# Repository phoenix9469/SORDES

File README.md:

## Sordes Motherboard SMT Version
### Schematic

### PCB

### 3D Top

### 3D Bottom

### Main MCU
ESP32_WROOM_32D
Internal Antenna
### Battery Charging
TP4056 Li-Ion Battery Charging Circuit(1A)
### DC-DC
SX1308 DC-DC Step Up Convertor(1.2MHz,2A)
3.7v~4.2v(Battery) to 5v(Logic)
### Weight measurement
HX711 24-Bit ADC for Weigh Scales
## Sordes LCD Board SMT Version
### Schematic

### PCB

### 3D Top

### 3D Bottom

### Main MCU
ESP32_WROOM_32D
Internal Antenna
### Pinmap
3.3V -> VCC  
GND -> GND  
GPIO15 -> CS  
GPIO4 -> RESET  
GPIO2 - > DC/RS  
GPIO23 -> SDI(MOSI),T_DIN  
GPIO18 -> SCK,T_CLK  
GPIO32 -> LED  
GPIO21 -> T_CS  
GPIO19 -> T_DO  
GPIO27 -> T_IRQ

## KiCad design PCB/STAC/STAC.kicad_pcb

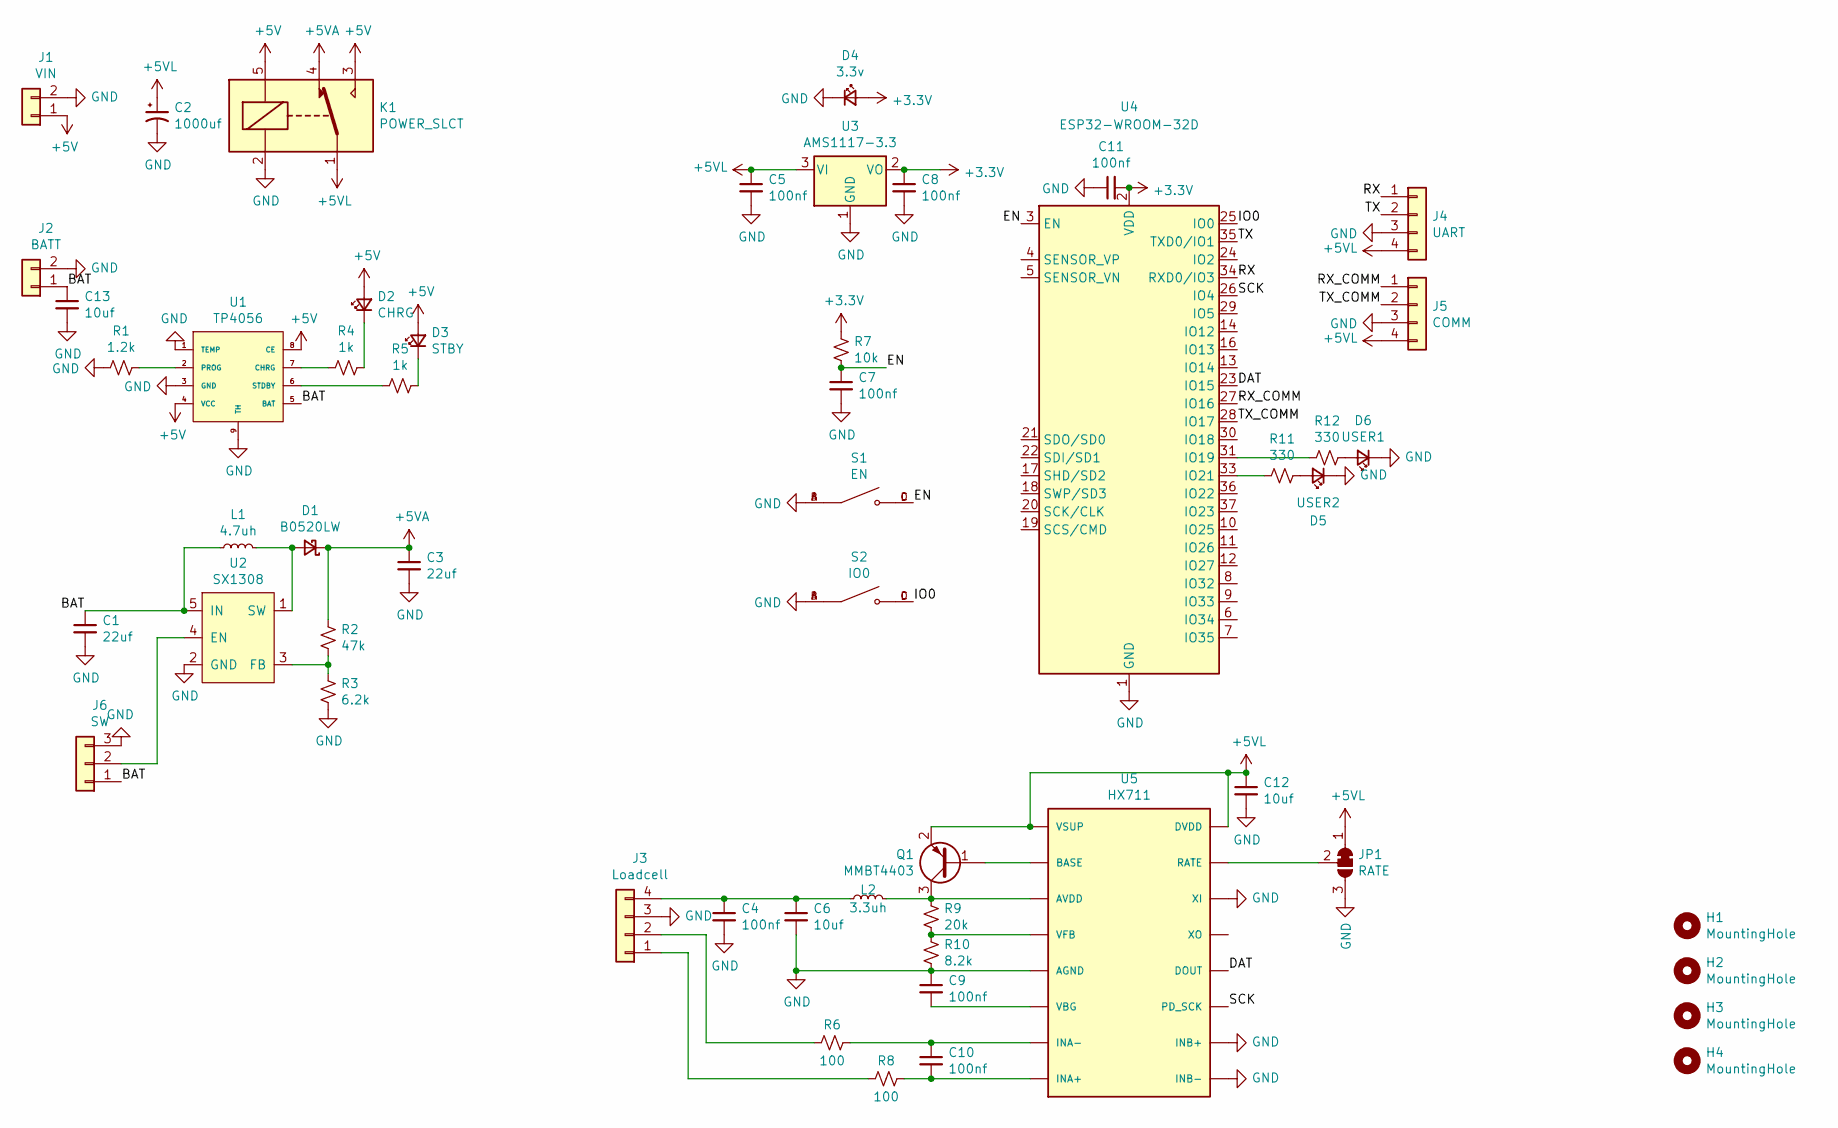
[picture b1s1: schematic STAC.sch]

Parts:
C1, C3: 22uf; C_0805_2012Metric
C2: 1000uf; CP_Elec_8x10
C4, C5, C7, C8, C9, C10, C11: 100nf; C_0603_1608Metric
C6, C12, C13: 10uf; C_0805_2012Metric
D1: B0520LW; D_SOD-123
D2: CHRG; LED_0603_1608Metric
D3: STBY; LED_0603_1608Metric
D4: 3.3v; LED_0603_1608Metric
D5: USER2; LED_0603_1608Metric
D6: USER1; LED_0603_1608Metric
H1, H2, H3, H4: MountingHole; MountingHole_3.2mm_M3
J1: VIN; Molex_PicoBlade_53261-0271_1x02-1MP_P1.25mm_Horizontal
J2: BATT; Molex_PicoBlade_53261-0271_1x02-1MP_P1.25mm_Horizontal
J3: Loadcell; Molex_PicoBlade_53261-0471_1x04-1MP_P1.25mm_Horizontal
J4: UART; Molex_PicoBlade_53261-0471_1x04-1MP_P1.25mm_Horizontal
J5: COMM; Molex_PicoBlade_53261-0471_1x04-1MP_P1.25mm_Horizontal
J6: SW; Molex_PicoBlade_53261-0371_1x03-1MP_P1.25mm_Horizontal
JP1: RATE; SolderJumper-3_P1.3mm_Bridged12_RoundedPad1.0x1.5mm_NumberL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
K1: POWER_SLCT; Relay_SPDT_SANYOU_SRD_Series_Form_C
L1: 4.7uh; L_6.3x6.3_H3
L2: 3.3uh; L_0603_1608Metric
Q1: MMBT4403; SOT-23
R1: 1.2k; R_0603_1608Metric
R2: 47k; R_0603_1608Metric
R3: 6.2k; R_0603_1608Metric
R4, R5: 1k; R_0603_1608Metric
R6, R8: 100; R_0603_1608Metric
R7: 10k; R_0603_1608Metric
R9: 20k; R_0603_1608Metric
R10: 8.2k; R_0603_1608Metric
R11, R12: 330; R_0603_1608Metric
S1: EN; SW_TS-1187A-B-A-B; PARTREV A0
S2: IO0; SW_TS-1187A-B-A-B; PARTREV A0
U1: TP4056; SOIC-8-1EP_3.9x4.9mm_P1.27mm_EP2.29x3mm_ThermalVias
U2: SX1308; SOT-23-6
U3: AMS1117-3.3; SOT-223-3_TabPin2
U4: ESP32-WROOM-32D; ESP32-WROOM-32
U5: HX711; SO-16_3.9x9.9mm_P1.27mm

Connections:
+3V3: C8.1, C11.2, D4.2 (A), R7.1, U3.2 (VO), U4.2 (VDD)
+5V: D2.2 (A), D3.2 (A), J1.1, K1.3, K1.5, U1.4 (VCC), U1.8 (CE)
+5VA: C3.1, D1.1 (K), K1.4, R2.1
+5VL: C2.1, C5.1, C12.1, J4.4, J5.4, JP1.1 (A), K1.1, Q1.2 (E), U3.3 (VI), U5.1 (VSUP), U5.16 (DVDD)
/BAT: C1.1, C13.1, J2.1, J6.1, L1.1, U1.5 (BAT), U2.5 (IN)
/DAT: U4.23 (IO15), U5.12 (DOUT)
/EN: C7.1, R7.2, S1.C, S1.D, U4.3 (EN)
/IO0: S2.C, S2.D, U4.25 (IO0)
/RX: J4.1, U4.34 (RXD0/IO3)
/RX_COMM: J5.1, U4.27 (IO16)
/SCK: U4.26 (IO4), U5.11 (PD_SCK)
/TX: J4.2, U4.35 (TXD0/IO1)
/TX_COMM: J5.2, U4.28 (IO17)
GND: C1.2, C2.2, C3.2, C4.2, C5.2, C6.2, C7.2, C8.2, C9.1, C11.1, C12.2, C13.2, D4.1 (K), D5.1 (K), D6.1 (K), J1.2, J2.2, J3.3, J4.3, J5.3, J6.3, JP1.3 (B), K1.2, R1.2, R3.2, R10.2, S1.A, S1.B, S2.A, S2.B, U1.1 (TEMP), U1.3 (GND), U1.9 (TH), U2.2 (GND), U3.1 (GND), U4.1 (GND), U4.15 (GND), U4.38 (GND), U4.39 (GND), U5.5 (AGND), U5.9 (INB-), U5.10 (INB+), U5.14 (XI)
unnamed: C4.1, C6.1, J3.4, L2.1
unnamed: C9.2, U5.6 (VBG)
unnamed: C10.1, R6.1, U5.7 (INA-)
unnamed: C10.2, R8.1, U5.8 (INA+)
unnamed: D1.2 (A), L1.2, U2.1 (SW)
unnamed: D2.1 (K), R4.1
unnamed: D3.1 (K), R5.1
unnamed: D5.2 (A), R11.1
unnamed: D6.2 (A), R12.1
unnamed: J3.1, R8.2
unnamed: J3.2, R6.2
unnamed: J6.2, U2.4 (EN)
unnamed: JP1.2 (C), U5.15 (RATE)
unnamed: L2.2, Q1.3 (C), R9.1, U5.3 (AVDD)
unnamed: Q1.1 (B), U5.2 (BASE)
unnamed: R1.1, U1.2 (PROG)
unnamed: R2.2, R3.1, U2.3 (FB)
unnamed: R4.2, U1.7 (CHRG)
unnamed: R5.2, U1.6 (STDBY)
unnamed: R9.2, R10.1, U5.4 (VFB)
unnamed: R11.2, U4.33 (IO21)
unnamed: R12.2, U4.31 (IO19)

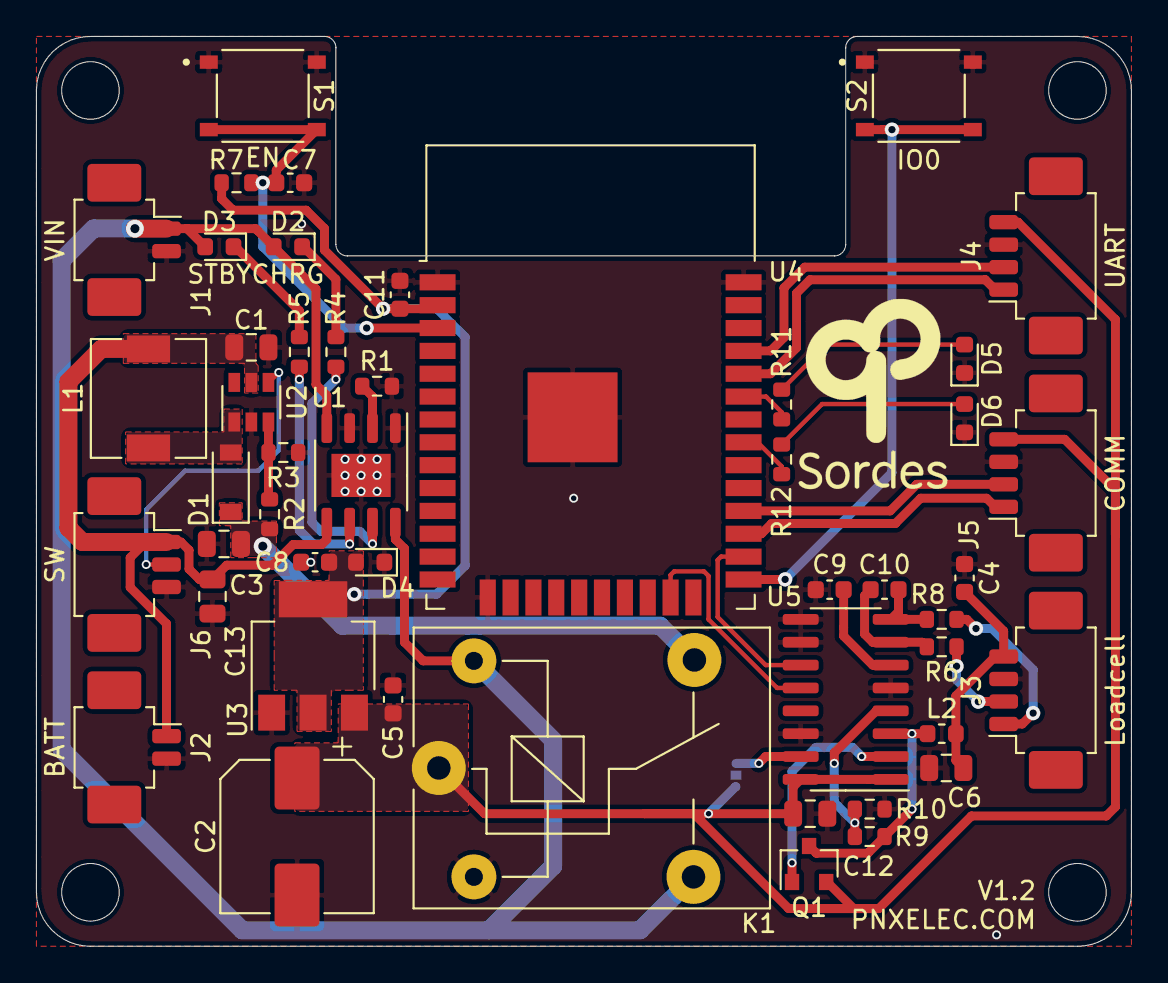
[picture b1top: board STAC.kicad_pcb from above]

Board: 2 copper layers, 60.8 x 50.5 mm, 53 parts (1 on the bottom side), 36 nets.

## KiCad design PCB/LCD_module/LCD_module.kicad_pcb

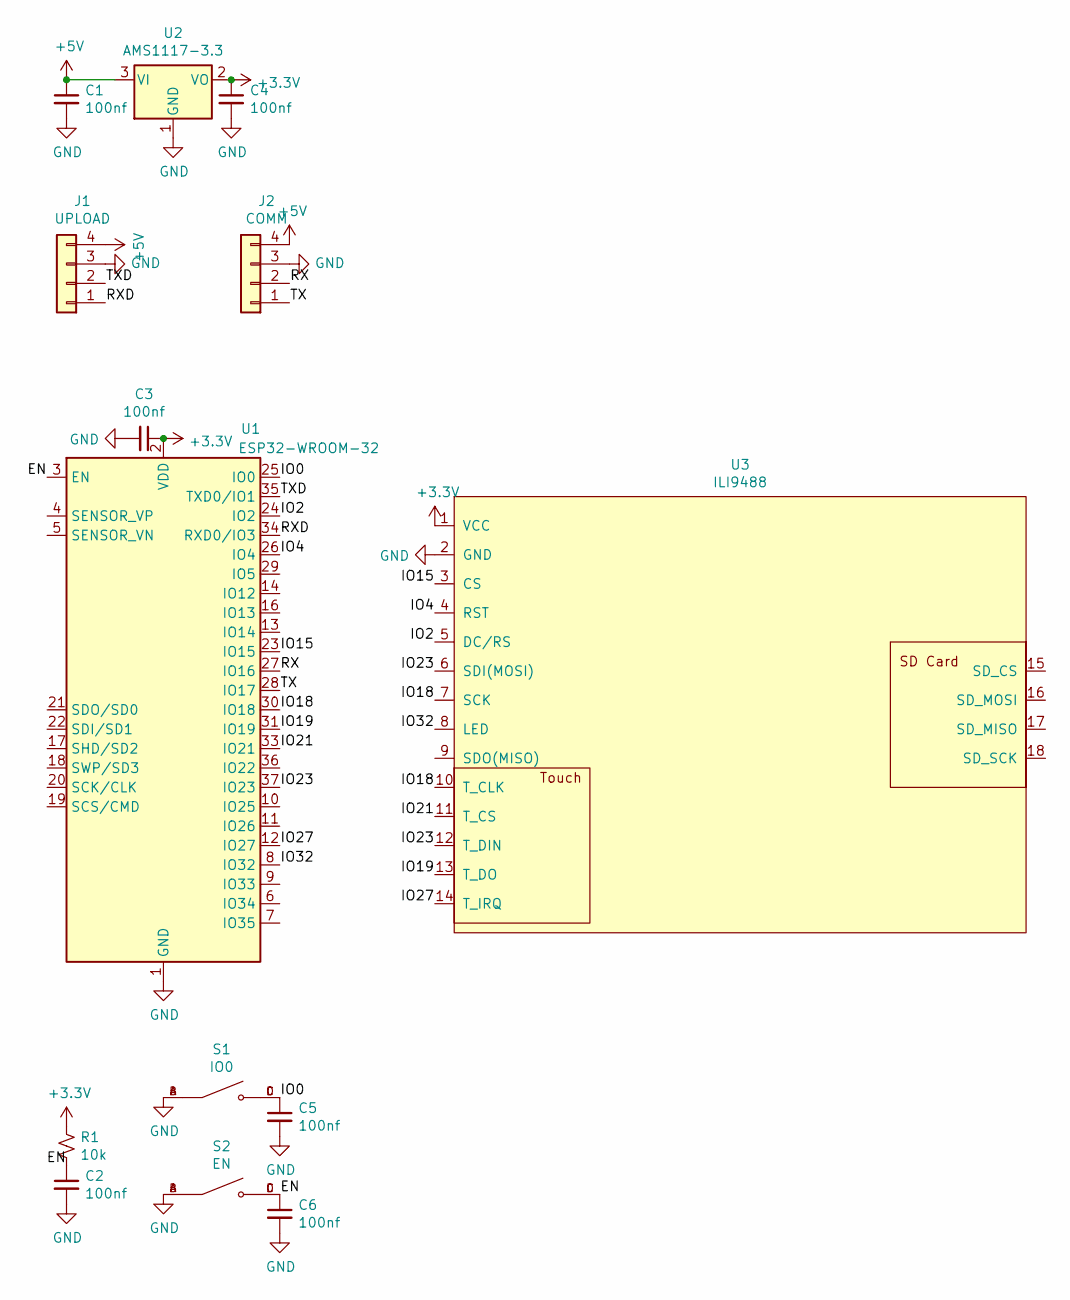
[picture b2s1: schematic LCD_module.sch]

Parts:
C1, C2, C3, C4, C5, C6: 100nf; C_0603_1608Metric
J1: UPLOAD; Molex_PicoBlade_53261-0471_1x04-1MP_P1.25mm_Horizontal
J2: COMM; Molex_PicoBlade_53261-0471_1x04-1MP_P1.25mm_Horizontal
R1: 10k; R_0603_1608Metric
S1: IO0; SW_TS-1187A-B-A-B; PARTREV A0
S2: EN; SW_TS-1187A-B-A-B; PARTREV A0
U1: ESP32-WROOM-32
U2: AMS1117-3.3; SOT-223-3_TabPin2
U3: ILI9488

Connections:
+3V3: C3.1, C4.1, R1.1, U1.2 (VDD), U2.2 (VO), U3.1 (VCC)
+5V: C1.1, J1.4, J2.4, U2.3 (VI)
/EN: C2.1, C6.1, R1.2, S2.C, S2.D, U1.3 (EN)
/IO0: C5.1, S1.C, S1.D, U1.25 (IO0)
/IO2: U1.24 (IO2), U3.5 (DC/RS)
/IO4: U1.26 (IO4), U3.4 (RST)
/IO15: U1.23 (IO15), U3.3 (CS)
/IO18: U1.30 (IO18), U3.7 (SCK), U3.10 (T_CLK)
/IO19: U1.31 (IO19), U3.13 (T_DO)
/IO21: U1.33 (IO21), U3.11 (T_CS)
/IO23: U1.37 (IO23), U3.6 (SDI(MOSI)), U3.12 (T_DIN)
/IO27: U1.12 (IO27), U3.14 (T_IRQ)
/IO32: U1.8 (IO32), U3.8 (LED)
/RX: J2.2, U1.27 (IO16)
/RXD: J1.1, U1.34 (RXD0/IO3)
/TX: J2.1, U1.28 (IO17)
/TXD: J1.2, U1.35 (TXD0/IO1)
GND: C1.2, C2.2, C3.2, C4.2, C5.2, C6.2, J1.3, J2.3, S1.A, S1.B, S2.A, S2.B, U1.1 (GND), U1.15 (GND), U1.38 (GND), U1.39 (GND), U2.1 (GND), U3.2 (GND)

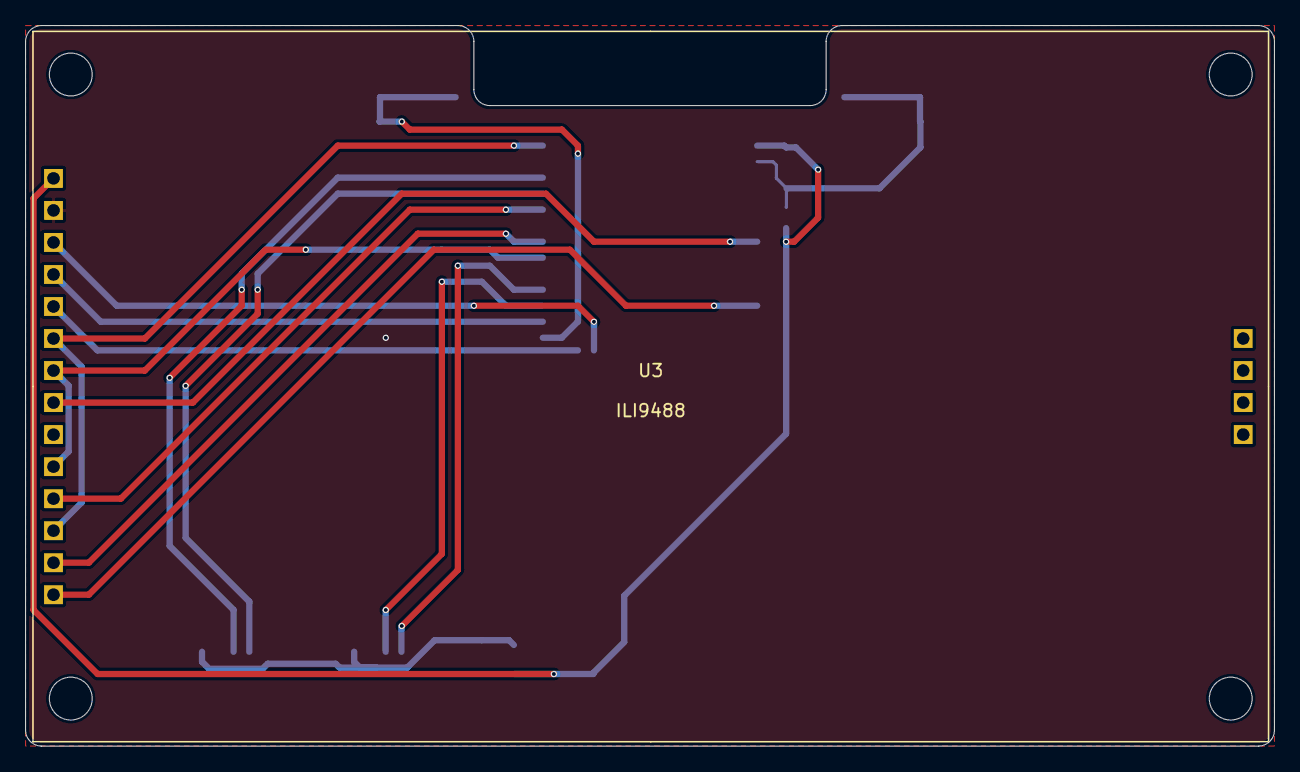
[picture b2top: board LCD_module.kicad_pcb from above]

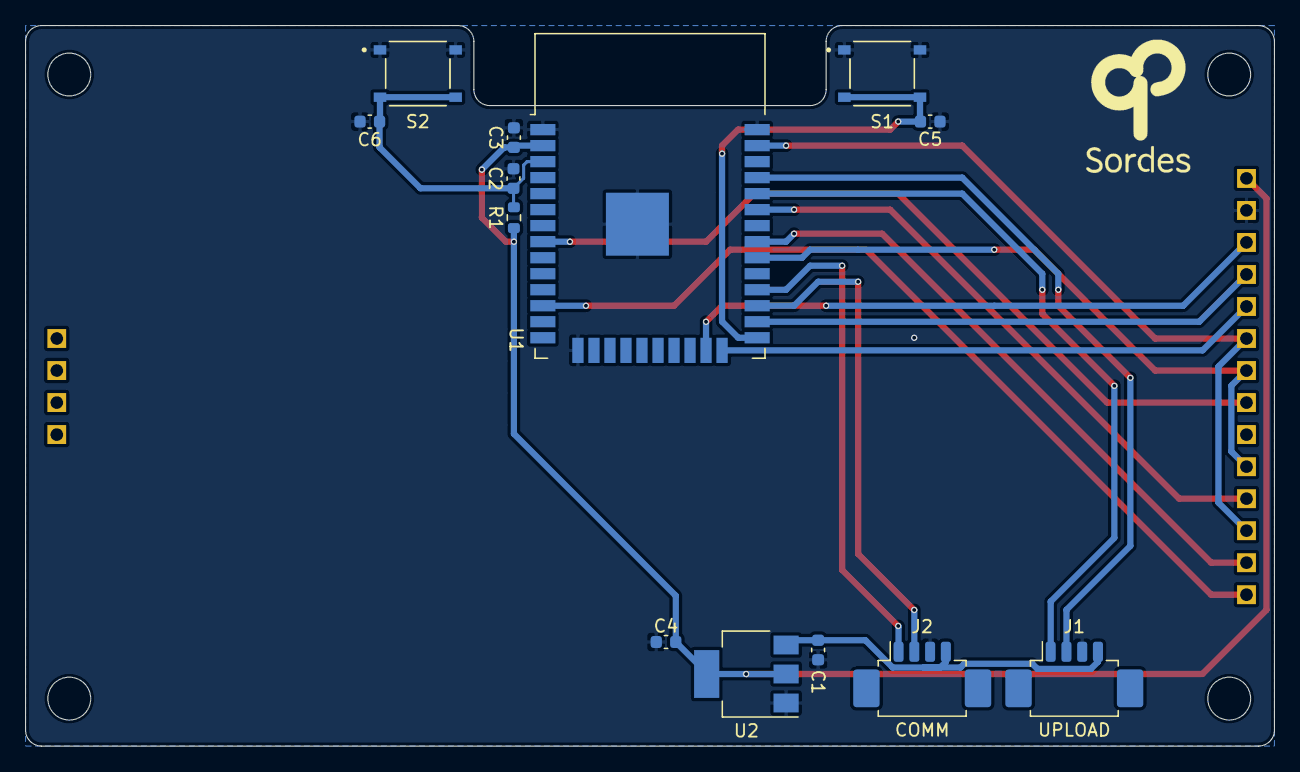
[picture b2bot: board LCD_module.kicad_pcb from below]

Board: 2 copper layers, 99.1 x 57.1 mm, 14 parts (13 on the bottom side), 18 nets.

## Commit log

2022-08-12 image update
2022-08-24 CIrcuit changed
